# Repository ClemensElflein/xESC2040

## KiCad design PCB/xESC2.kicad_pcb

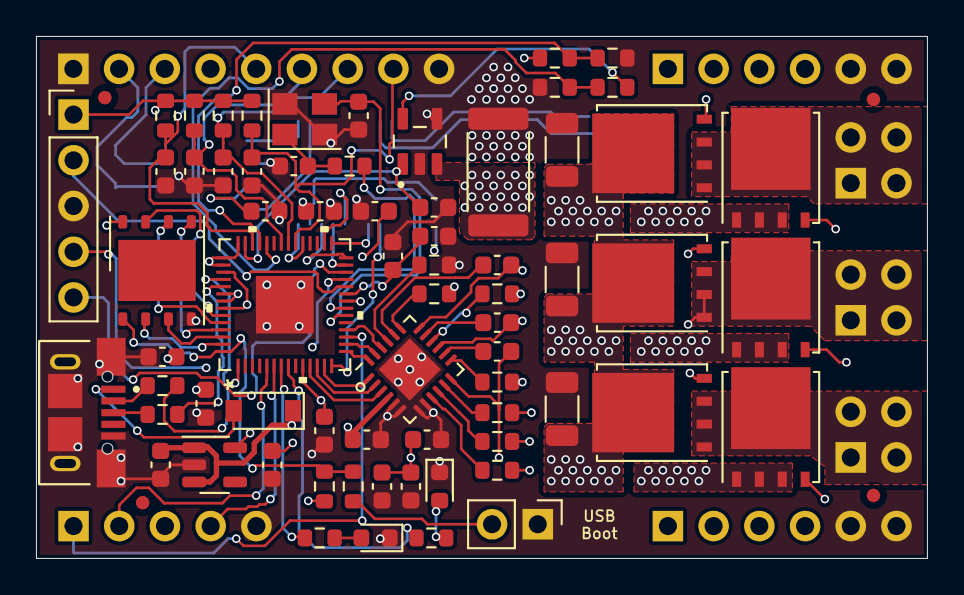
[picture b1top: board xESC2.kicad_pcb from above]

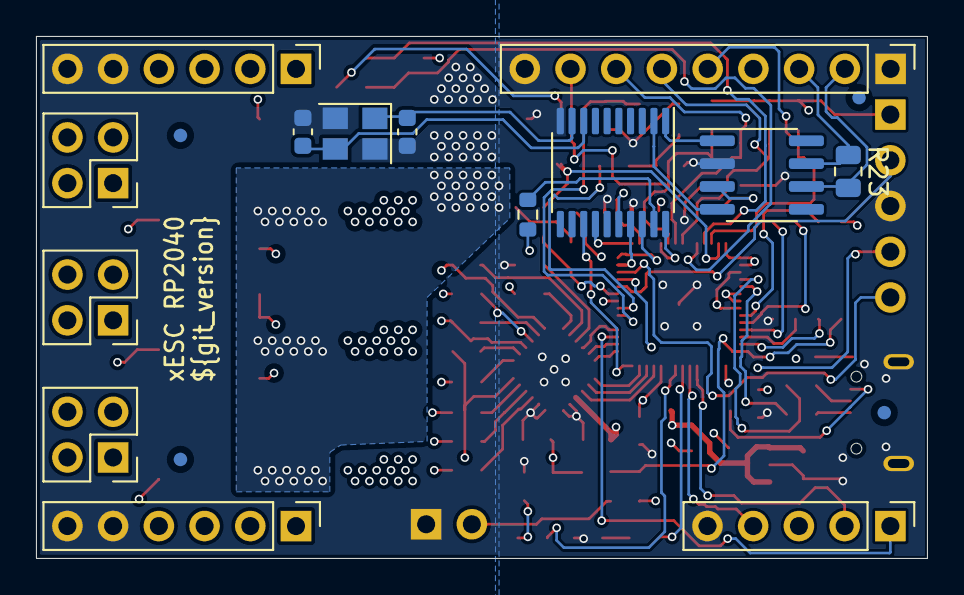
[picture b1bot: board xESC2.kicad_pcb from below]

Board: 4 copper layers, 49.5 x 29.0 mm, 90 parts (18 on the bottom side), 75 nets.

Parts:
C1, C2, C3, C4, C8, C9, C10, C11, C12, C13, C14, C15, C16, C20: .1uF; C_0603_1608Metric
C5, C6, C28, C29: 27pF; C_0603_1608Metric
C7, C17: 1uF; C_0603_1608Metric
C18, C26, C27: 2.2uF/50V; C_1206_3216Metric
C19: 100nF; C_0603_1608Metric
C21, C22, C23: 470nF/16V; C_0603_1608Metric
C24, C25: 4.7uF/16V; C_0603_1608Metric
D1: D_Schottky; D_SOD-123
D2: LED GREEN; LED_0603_1608Metric
D3: LED RED; LED_0603_1608Metric
FID1, FID2, FID3, FID4, FID5, FID6, FID7, FID8: Fiducial; Fiducial_0.75mm_Mask1.5mm
J1: Conn_01x09_Male; PinHeader_1x09_P2.54mm_Vertical
J2: U254-051T-4BH83-F1S; XKB_U254-051T-4BH83-F1S
J3, J4: Conn_01x05_Male; PinHeader_1x05_P2.54mm_Vertical
J5: Conn_01x02; PinHeader_1x02_P2.54mm_Vertical
J6, J9, J10: Conn_02x02_Counter_Clockwise; PinHeader_2x02_P2.54mm_Vertical
J7, J8: Conn_01x06_Male; PinHeader_1x06_P2.54mm_Vertical
Q1, Q2, Q3, Q4, Q5, Q6: BSC026N08NS5; TDSON-8-1
R1, R9, R14, R24: 10K; R_0603_1608Metric
R2, R3: 22R; R_0603_1608Metric
R4, R5, R6: 2k2; R_0603_1608Metric
R7: 22k; R_0603_1608Metric
R8: 1k5; R_0603_1608Metric
R10, R11: 150R; R_0603_1608Metric
R12, R13: 1K; R_0603_1608Metric
R15, R16, R19, R20, R21, R22: 2R2; R_0603_1608Metric
R17: DNP; R_0603_1608Metric
R18: 3mR; R_2512_6332Metric
R23: 120R; R_0805_2012Metric
TH1: Thermistor_NTC; R_0603_1608Metric
U1: RP2040
U2: W25Q128JVP; WSON-8-1EP_6x5mm_P1.27mm_EP3.4x4.3mm
U3: DRV8300DRGER; VQFN-24-1EP_4x4mm_P0.5mm_EP2.45x2.45mm
U4: INA180A4; SOT95P280X145-5N
U5: XC6220B331MR; SOT-23-5
U6: SN65HVD232; SOIC-8_3.9x4.9mm_P1.27mm
U7: MCP2515-xST; TSSOP-20_4.4x6.5mm_P0.65mm
Y1: 12MHz; Crystal_SMD_3225-4Pin_3.2x2.5mm
Y2: Crystal_GND24; Crystal_SMD_3225-4Pin_3.2x2.5mm

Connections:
+3V3: C7.1, C8.1, C9.1, C10.1, C11.1, C12.1, C13.1, C14.1, C25.1, J3.1, R1.1, R4.1, R5.1, R6.1, R14.2, R24.1, TH1.1, U1.1 (IOVDD), U1.10 (IOVDD), U1.22 (IOVDD), U1.33 (IOVDD), U1.42 (IOVDD), U1.43 (ADC_AVDD), U1.44 (VREG_VIN), U1.48 (USB_VDD), U1.49 (IOVDD), U2.8 (VCC), U4.5 (VS), U5.5 (VOUT), U6.3 (VCC), U7.20 (VDD)
+5V: C19.1, C24.1, D1.1 (K), J1.4, J7.3, J7.4, J8.3, J8.4, U3.4 (GVDD), U5.1 (VIN), U5.3 (CE)
/CAN/INT: U1.14 (GPIO11), U7.13 (~INT)
/CAN/MISO: U1.27 (GPIO16), U7.17 (SO)
/CAN/MOSI: U1.30 (GPIO19), U7.16 (SI)
/CAN/SCK: U1.29 (GPIO18), U7.14 (SCK)
/CAN/~CS: U1.28 (GPIO17), U7.18 (~CS)
/CAN_N: J1.2, R23.2, U6.6 (CANL)
/CAN_P: J1.3, R23.1, U6.7 (CANH)
/HALL1: C2.1, J1.6, R4.2, U1.36 (GPIO24)
/HALL2: C3.1, J1.7, R5.2, U1.35 (GPIO23)
/HALL3: C4.1, J1.8, R6.2, U1.34 (GPIO22)
/LED_GREEN: R10.1, U1.8 (GPIO6)
/LED_RED: R11.1, U1.7 (GPIO5)
/MCU/1.1V: C15.1, C16.1, C17.1, U1.23 (DVDD), U1.45 (VREG_VOUT), U1.50 (DVDD)
/MCU/CURRENT_SENSE: C20.1, U1.41 (GPIO29/ADC3), U4.1 (OUT)
/MCU/QSPI_SD0: U1.53 (QSPI_SD0), U2.5 (DI(IO0))
/MCU/QSPI_SD1: U1.55 (QSPI_SD1), U2.2 (DO(IO1))
/MCU/QSPI_SD2: U1.54 (QSPI_SD2), U2.3 (IO2)
/MCU/QSPI_SD3: U1.51 (QSPI_SD3), U2.7 (IO3)
/MCU/Reset: J3.5, U1.26 (RUN)
/MCU/SHUTDOWN: J4.1, U1.17 (GPIO14)
/MCU/SWDCLK: J3.2, U1.24 (SWCLK)
/MCU/SWDIO: J3.4, U1.25 (SWDIO)
/MCU/UART_RX: J4.4, U1.6 (GPIO4)
/MCU/UART_TX: J4.2, U1.5 (GPIO3)
/MCU/UH: U1.15 (GPIO12), U3.24 (INHC)
/MCU/UL: U1.11 (GPIO8), U3.3 (INLC)
/MCU/VH: U1.16 (GPIO13), U3.23 (INHB)
/MCU/VL: U1.12 (GPIO9), U3.2 (INLB)
/MCU/WH: U1.18 (GPIO15), U3.22 (INHA)
/MCU/WL: U1.13 (GPIO10), U3.1 (INLA)
/MCU/Xin: C5.2, U1.20 (XIN), Y1.3
/MCU/Xout: R12.2, U1.21 (XOUT)
/PCB_TEMP: R9.1, TH1.2, U1.38 (GPIO26/ADC0)
/Power/DRV_U: C23.1, J6.1, J6.2, J6.3, J6.4, Q1.1 (S), Q1.2 (S), Q1.3 (S), Q2.5 (D), U3.12 (SHC)
/Power/DRV_V: C22.1, J9.1, J9.2, J9.3, J9.4, Q3.1 (S), Q3.2 (S), Q3.3 (S), Q4.5 (D), U3.15 (SHB)
/Power/DRV_W: C21.1, J10.1, J10.2, J10.3, J10.4, Q5.1 (S), Q5.2 (S), Q5.3 (S), Q6.5 (D), U3.18 (SHA)
/Power/HSU: R15.2, U3.13 (GHC)
/Power/HSV: R19.2, U3.16 (GHB)
/Power/HSW: R21.2, U3.19 (GHA)
/Power/LSU: R16.2, U3.9 (GLC)
/Power/LSV: R20.2, U3.10 (GLB)
/Power/LSW: R22.2, U3.11 (GLA)
/Power/MOSFET/MOSFET_GND: Q2.1 (S), Q2.2 (S), Q2.3 (S), Q4.1 (S), Q4.2 (S), Q4.3 (S), Q6.1 (S), Q6.2 (S), Q6.3 (S), R18.1, U4.3 (IN+)
/TEMP_MOTOR: C1.1, J1.5, R1.2, U1.40 (GPIO28/ADC2)
/USB_DM: R2.1, U1.46 (USB_DM)
/USB_DP: R3.1, U1.47 (USB_DP)
/VM: C18.1, C26.1, C27.1, J7.1, J7.2, J8.1, J8.2, Q1.5 (D), Q3.5 (D), Q5.5 (D), R7.1
/V_M_FILTERED: R7.2, R8.1, U1.39 (GPIO27/ADC1)
GND: C1.2, C2.2, C3.2, C4.2, C5.1, C6.1, C7.2, C8.2, C9.2, C10.2, C11.2, C12.2, C13.2, C14.2, C15.2, C16.2, C17.2, C18.2, C19.2, C20.2, C24.2, C25.2, C26.2, C27.2, C28.1, C29.1, D2.1 (K), D3.1 (K), J1.1, J1.9, J2.5 (GND), J2.S1 (SHIELD), J2.S2 (SHIELD), J2.S3 (SHIELD), J2.S4 (SHIELD), J2.S5 (SHIELD), J2.S6 (SHIELD), J3.3, J4.5, J5.1, J7.5, J7.6, J8.5, J8.6, R8.2, R9.2, R17.2, R18.2, U1.57 (GND), U2.4 (GND), U3.5 (MODE), U3.6 (GND), U3.7 (NC), U3.8 (NC), U3.25 (PowerPAD), U4.2 (GND), U4.4 (IN-), U5.2 (GND), U6.2 (GND), U7.10 (VSS), Y1.2, Y1.4, Y2.2, Y2.4
unnamed: C6.2, R12.1, Y1.1
unnamed: C21.2, U3.20 (BSTA)
unnamed: C22.2, U3.17 (BSTB)
unnamed: C23.2, U3.14 (BSTC)
unnamed: C28.2, U7.8 (OSC2), Y2.3
unnamed: C29.2, U7.9 (OSC1), Y2.1
unnamed: D1.2 (A), J2.1 (VCC)
unnamed: D2.2 (A), R10.2
unnamed: D3.2 (A), R11.2
unnamed: J2.2 (D-), R2.2
unnamed: J2.3 (D+), R3.2
unnamed: J5.2, R13.1
unnamed: Q1.4 (G), R15.1
unnamed: Q2.4 (G), R16.1
unnamed: Q3.4 (G), R19.1
unnamed: Q4.4 (G), R20.1
unnamed: Q5.4 (G), R21.1
unnamed: Q6.4 (G), R22.1
unnamed: R13.2, R14.1, U1.56 (QSPI_SS_N), U2.1 (~CS)
unnamed: R17.1, U3.21 (DT)
unnamed: R24.2, U7.19 (~RESET)
unnamed: U1.52 (QSPI_SCLK), U2.6 (CLK)
unnamed: U6.1 (D), U7.1 (TXCAN)
unnamed: U6.4 (R), U7.2 (RXCAN)

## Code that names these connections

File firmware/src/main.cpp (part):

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
float readCurrent()
{
  return (float)analogRead(PIN_CURRENT_SENSE) * (3.3f / 4096.0f) / (CURRENT_SENSE_GAIN * R_SHUNT);
}

void setup()
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  pinMode(PIN_UL, OUTPUT);
  pinMode(PIN_VL, OUTPUT);
  pinMode(PIN_WL, OUTPUT);
  pinMode(PIN_LED_RED, OUTPUT);
  pinMode(PIN_LED_GREEN, OUTPUT);

  digitalWrite(PIN_LED_RED, HIGH);
  digitalWrite(PIN_LED_GREEN, LOW);

  digitalWrite(PIN_UH, LOW);
  digitalWrite(PIN_VH, LOW);
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  if (duty_setpoint_ramped > current_limit_duty)
  {

    digitalWrite(PIN_LED_GREEN, HIGH);
    duty = current_limit_duty;
  }
  else if (duty_setpoint_ramped < -current_limit_duty)
  {

    digitalWrite(PIN_LED_GREEN, HIGH);
    duty = -current_limit_duty;
  }
  else
  {
    digitalWrite(PIN_LED_GREEN, LOW);
    duty = duty_setpoint_ramped;
  }

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
float readMotorTemp()
{
  return NTC_TEMP_MOTOR((float)analogRead(PIN_TEMP_MOTOR));
}

float readPcbTemp()
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
  if(faults) {
    // We have faults, set them in the status
    digitalWrite(PIN_LED_RED, HIGH);
    status.fault_code = faults;
    last_fault_millis = millis();
  } else if(faults == 0 && status.fault_code != 0) {
    // We want to reset faults. Only reset if MIN_FAULT_TIME_MILLIS has passed or if it was watchdog fault only
    if(status.fault_code == FAULT_WATCHDOG || millis() - last_fault_millis > MIN_FAULT_TIME_MILLIS) {
      digitalWrite(PIN_LED_RED, LOW);
      status.fault_code = 0;
    }
  }
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
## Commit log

2022-07-14 chore: rearrange folders
2022-07-14 feat(GH): KiBot configuration
2022-07-15 feat(kibot): KiBot filters to resemble KiCad
2022-07-15 fix: mark C28, C29, R24 as `+can`
2022-07-15 feat(GH): action on tag and commit
2022-07-20 Update MCU.kicad_sch
    fixed crystal ref
2022-07-20 deploy: 7a019a21196d850f052f78335eb38aa9e9dc3469
2022-07-24 fix(VREG): update C24,C25 value to 10uF to match DigiKey
2022-08-14 fix(power): update PNs for R18 shunt
2022-08-26 newer integration does not need platform specific tools anymore
2022-08-26 added .1uF for C2-C4
2022-09-01 fix(pcb): reference RP2040_QFN from GrabCAD
2022-09-01 typo: thermistor
2022-09-02 fix: regenerated STEP rendering
2022-09-30 fix: remove testing leftover
2023-01-18 Added tacho_absolute and direction
2023-01-18 Tiny sturct order change
2023-01-19 Fixed direction computation and comments
2023-01-19 Added FW binary
2023-05-25 Flip direction
2024-07-21 Flip direction (#10)

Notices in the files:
firmware/src/main.cpp:
Copyright (c) 2022 Clemens Elflein. All rights reserved.
This work is licensed under a Creative Commons Attribution-NonCommercial-ShareAlike 4.0 International License.
parts and their libraries:
Copyright 2021 Accelerated Designs. All rights reserved.
